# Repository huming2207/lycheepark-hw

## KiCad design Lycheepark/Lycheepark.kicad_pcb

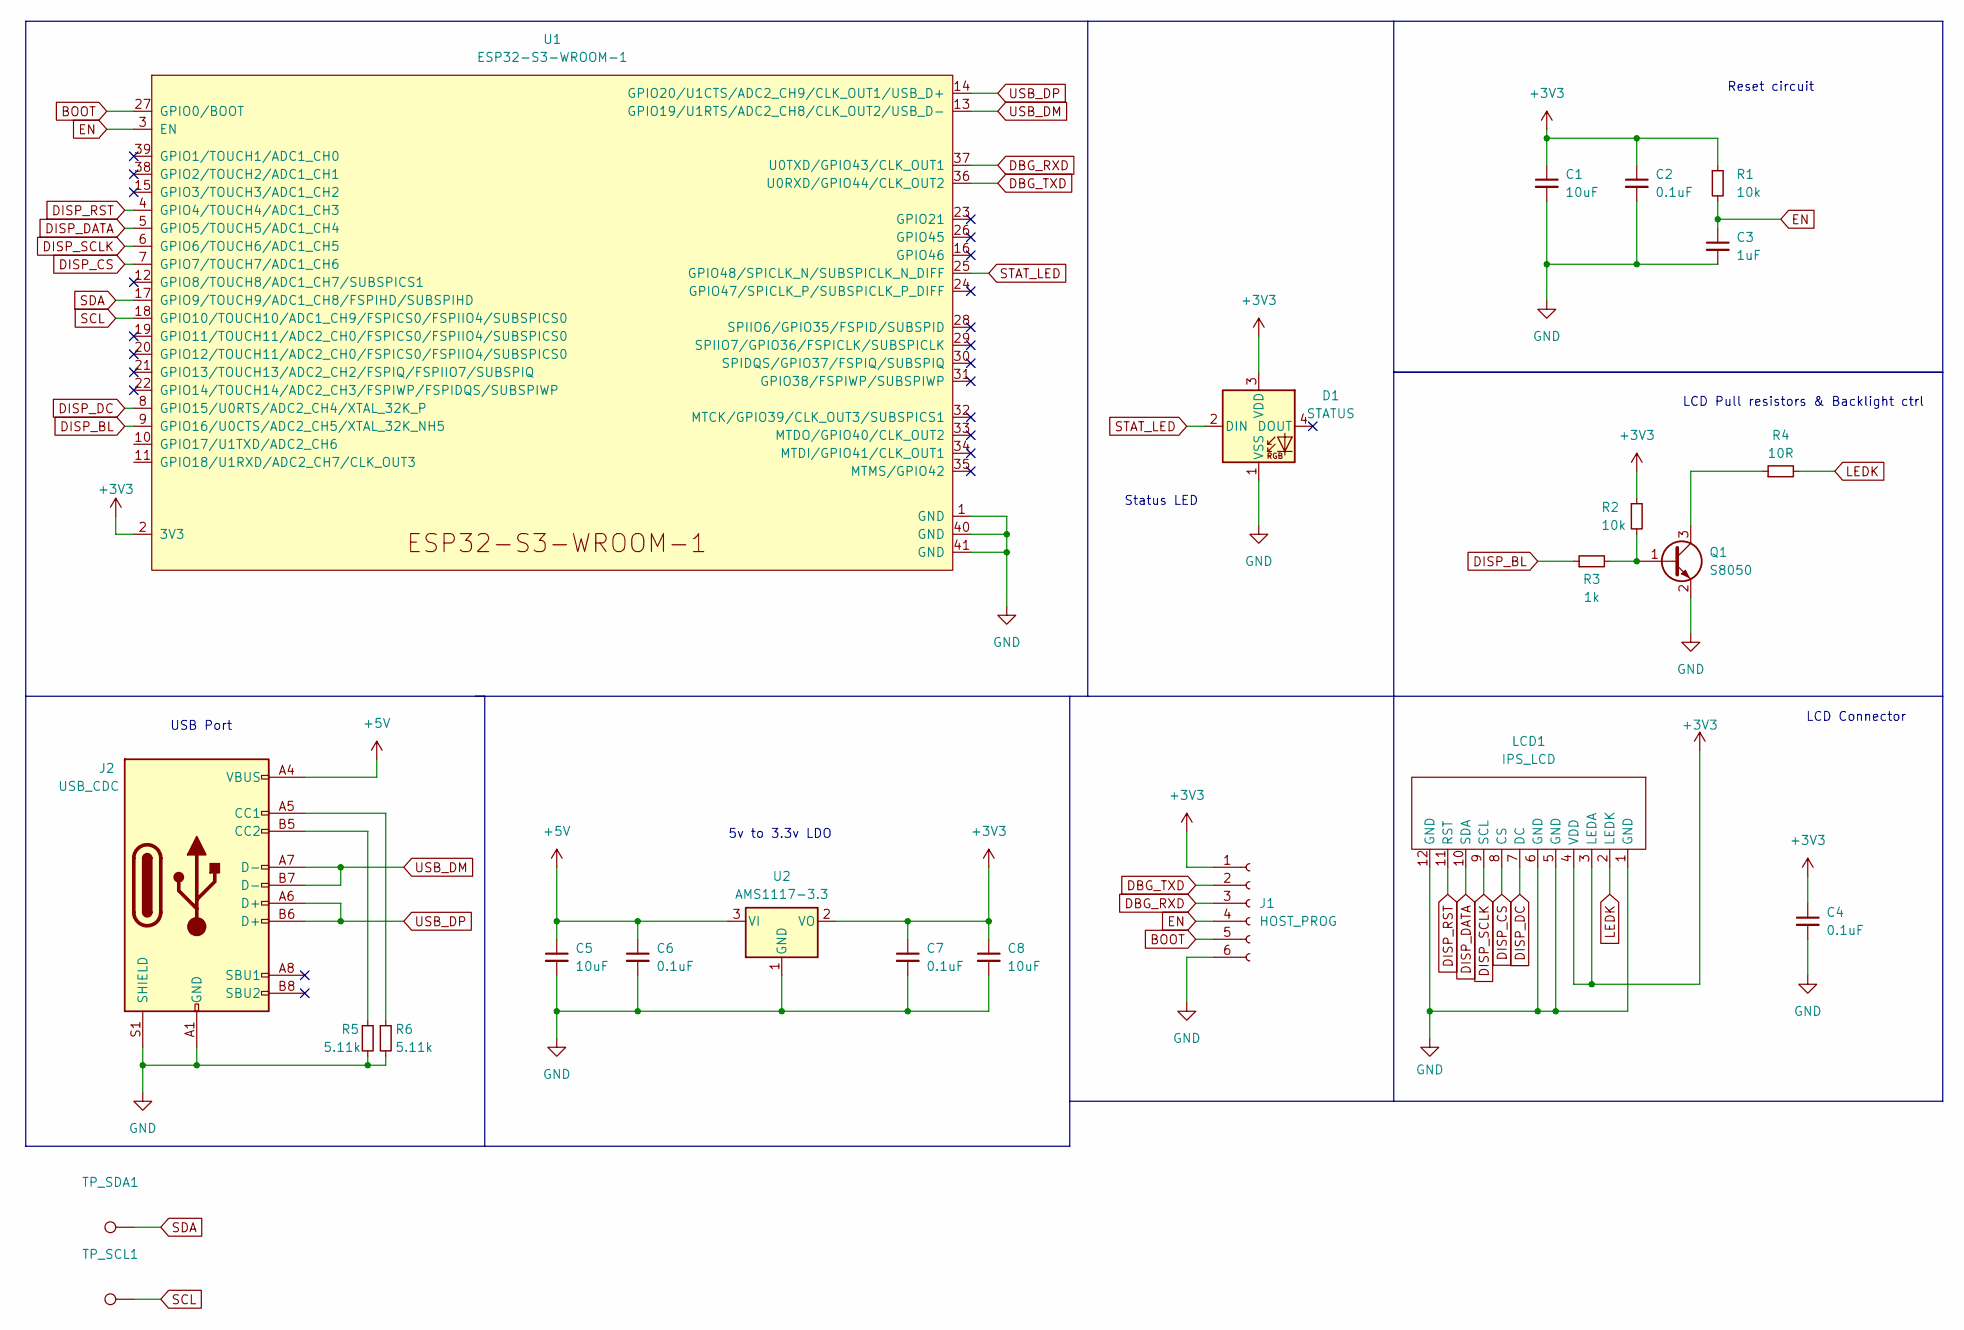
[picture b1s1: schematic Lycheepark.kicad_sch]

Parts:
C1, C5, C8: 10uF; C_0805_2012Metric_Pad1.18x1.45mm_HandSolder
C2, C4, C6, C7: 0.1uF; C_0805_2012Metric_Pad1.18x1.45mm_HandSolder
C3: 1uF; C_0805_2012Metric_Pad1.18x1.45mm_HandSolder
D1: STATUS; LED_SK6812_PLCC4_5.0x5.0mm_P3.2mm
J1: HOST_PROG; PinSocket_1x06_P1.27mm_Vertical
J2: USB_CDC; USB_C_Receptacle_HRO_TYPE-C-31-M-12
LCD1: IPS_LCD; ST7789V_1.5_IPS_PG04
Q1: S8050; SOT-23
R1, R2: 10k; R_0805_2012Metric_Pad1.20x1.40mm_HandSolder
R3: 1k; R_0805_2012Metric_Pad1.20x1.40mm_HandSolder
R4: 10R; R_0805_2012Metric_Pad1.20x1.40mm_HandSolder
R5, R6: 5.11k; R_0805_2012Metric_Pad1.20x1.40mm_HandSolder
TP_SCL1: (no value)
TP_SDA1: (no value)
U1: ESP32-S3-WROOM-1
U2: AMS1117-3.3; SOT-223-3_TabPin2

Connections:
+3V3: C1.1, C2.1, C4.1, C7.1, C8.1, D1.3 (VDD), J1.1, LCD1.3 (LEDA), LCD1.4 (VDD), R1.1, R2.1, U1.2 (3V3), U2.2 (VO)
+5V: C5.1, C6.1, J2.A4 (VBUS), J2.A9 (VBUS), J2.B4 (VBUS), J2.B9 (VBUS), U2.3 (VI)
BOOT: J1.5, U1.27 (GPIO0/BOOT)
DBG_RXD: J1.3, U1.37 (U0TXD/GPIO43/CLK_OUT1)
DBG_TXD: J1.2, U1.36 (U0RXD/GPIO44/CLK_OUT2)
DISP_BL: R3.1, U1.9 (GPIO16/U0CTS/ADC2_CH5/XTAL_32K_NH5)
DISP_CS: LCD1.8 (CS), U1.7 (GPIO7/TOUCH7/ADC1_CH6)
DISP_DATA: LCD1.10 (SDA), U1.5 (GPIO5/TOUCH5/ADC1_CH4)
DISP_DC: LCD1.7 (DC), U1.8 (GPIO15/U0RTS/ADC2_CH4/XTAL_32K_P)
DISP_RST: LCD1.11 (RST), U1.4 (GPIO4/TOUCH4/ADC1_CH3)
DISP_SCLK: LCD1.9 (SCL), U1.6 (GPIO6/TOUCH6/ADC1_CH5)
EN: C3.1, J1.4, R1.2, U1.3 (EN)
GND: C1.2, C2.2, C3.2, C4.2, C5.2, C6.2, C7.2, C8.2, D1.1 (VSS), J1.6, J2.A1 (GND), J2.A12 (GND), J2.B1 (GND), J2.B12 (GND), J2.S1 (SHIELD), LCD1.1 (GND), LCD1.5 (GND), LCD1.6 (GND), LCD1.12 (GND), Q1.2 (E), R5.2, R6.2, U1.1 (GND), U1.40 (GND), U1.41 (GND), U2.1 (GND)
LEDK: LCD1.2 (LEDK), R4.2
unnamed: J2.A5 (CC1), R6.1
unnamed: J2.B5 (CC2), R5.1
unnamed: Q1.1 (B), R2.2, R3.2
unnamed: Q1.3 (C), R4.1
SCL: TP_SCL1.1, U1.18 (GPIO10/TOUCH10/ADC1_CH9/FSPICS0/FSPIIO4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); also elsewhere on the board
SDA: TP_SDA1.1, U1.17 (GPIO9/TOUCH9/ADC1_CH8/FSPIHD/SUBSPIHD); also elsewhere on the board
STAT_LED: D1.2 (DIN), U1.25 (GPIO48/SPICLK_N/SUBSPICLK_N_DIFF)
USB_DM: J2.A7 (D-), J2.B7 (D-), U1.13 (GPIO19/U1RTS/ADC2_CH8/CLK_OUT2/USB_D-)
USB_DP: J2.A6 (D+), J2.B6 (D+), U1.14 (GPIO20/U1CTS/ADC2_CH9/CLK_OUT1/USB_D+)

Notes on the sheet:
5v to 3.3v LDO
LCD Pull resistors & Backlight ctrl
USB Port
Reset circuit
Status LED
LCD Connector

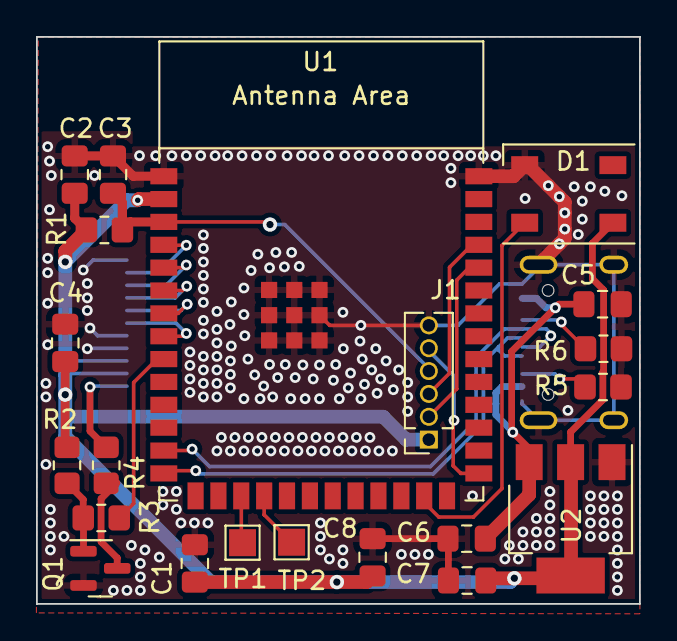
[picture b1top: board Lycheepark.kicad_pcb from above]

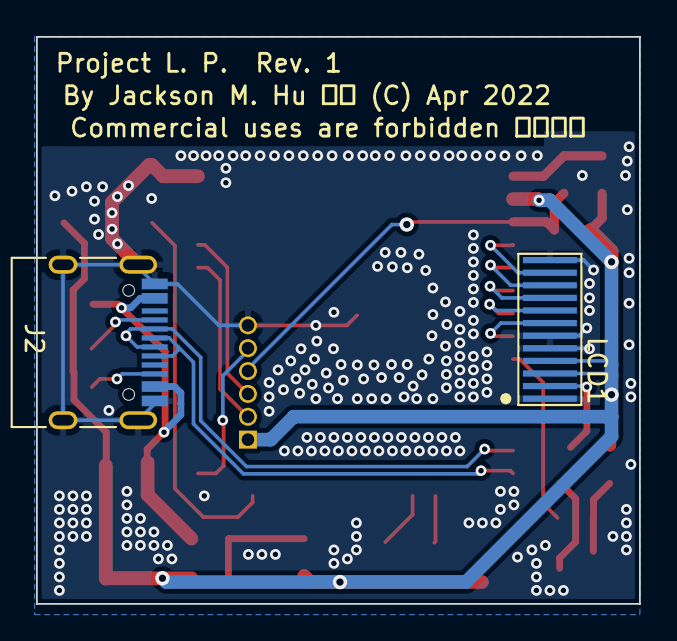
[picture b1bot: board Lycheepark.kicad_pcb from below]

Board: 2 copper layers, 33.5 x 31.5 mm, 23 parts (2 on the bottom side), 23 nets.

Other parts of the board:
TP1, TP2: TestPoint; TestPoint_Pad_1.5x1.5mm

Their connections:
SCL: TP2.1; also elsewhere on the board
SDA: TP1.1; also elsewhere on the board

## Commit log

2022-03-31 init
2022-03-31 Init kicad project
2022-03-31 Create LICENSE
2022-04-30 Force sync
2022-04-30 Rev 2: init
